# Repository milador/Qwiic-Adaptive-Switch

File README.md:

# Qwiic-Adaptive-Switch

Qwiic-Adaptive-Switch modules provide an easy way to create your own adaptive switch input or output boxes through Qwiic or STEMMA QT ecosystem. Qwiic Adaptive Switch modules can be connected to any Qwiic enabled board to create an adaptive switch box.

You can find more information about <a href="https://www.sparkfun.com/qwiic">Qwiic Connect System</a> at SparkFun official website.

Qwiic-Adaptive-Switch modules use Qwiic/JST-SH-4Pin connector and IC2 interface to communicate with main microcontroller which means you can connect multiple switch modules by daisy chaining them. It's using TCA9534 bus expander.

## Qwiic-Adaptive-Switch-Input

Top View: 

Bottom View:

## Qwiic-Adaptive-Switch-Output

Top View: 

Bottom View:

## Risk Assessment

The Risk Assessment documents are located under [Documents](./Documents/) directory. 

## License

### MIT License

Copyright (c) 2021 milador

Permission is hereby granted, free of charge, to any person obtaining a copy of this software and associated documentation files (the "Software"), to deal in the Software without restriction, including without limitation the rights to use, copy, modify, merge, publish, distribute, sublicense, and/or sell copies of the Software, and to permit persons to whom the Software is furnished to do so, subject to the following conditions:

The above copyright notice and this permission notice shall be included in all copies or substantial portions of the Software.

THE SOFTWARE IS PROVIDED "AS IS", WITHOUT WARRANTY OF ANY KIND, EXPRESS OR IMPLIED, INCLUDING BUT NOT LIMITED TO THE WARRANTIES OF MERCHANTABILITY, FITNESS FOR A PARTICULAR PURPOSE AND NONINFRINGEMENT. IN NO EVENT SHALL THE AUTHORS OR COPYRIGHT HOLDERS BE LIABLE FOR ANY CLAIM, DAMAGES OR OTHER LIABILITY, WHETHER IN AN ACTION OF CONTRACT, TORT OR OTHERWISE, ARISING FROM, OUT OF OR IN CONNECTION WITH THE SOFTWARE OR THE USE OR OTHER DEALINGS IN THE SOFTWARE.

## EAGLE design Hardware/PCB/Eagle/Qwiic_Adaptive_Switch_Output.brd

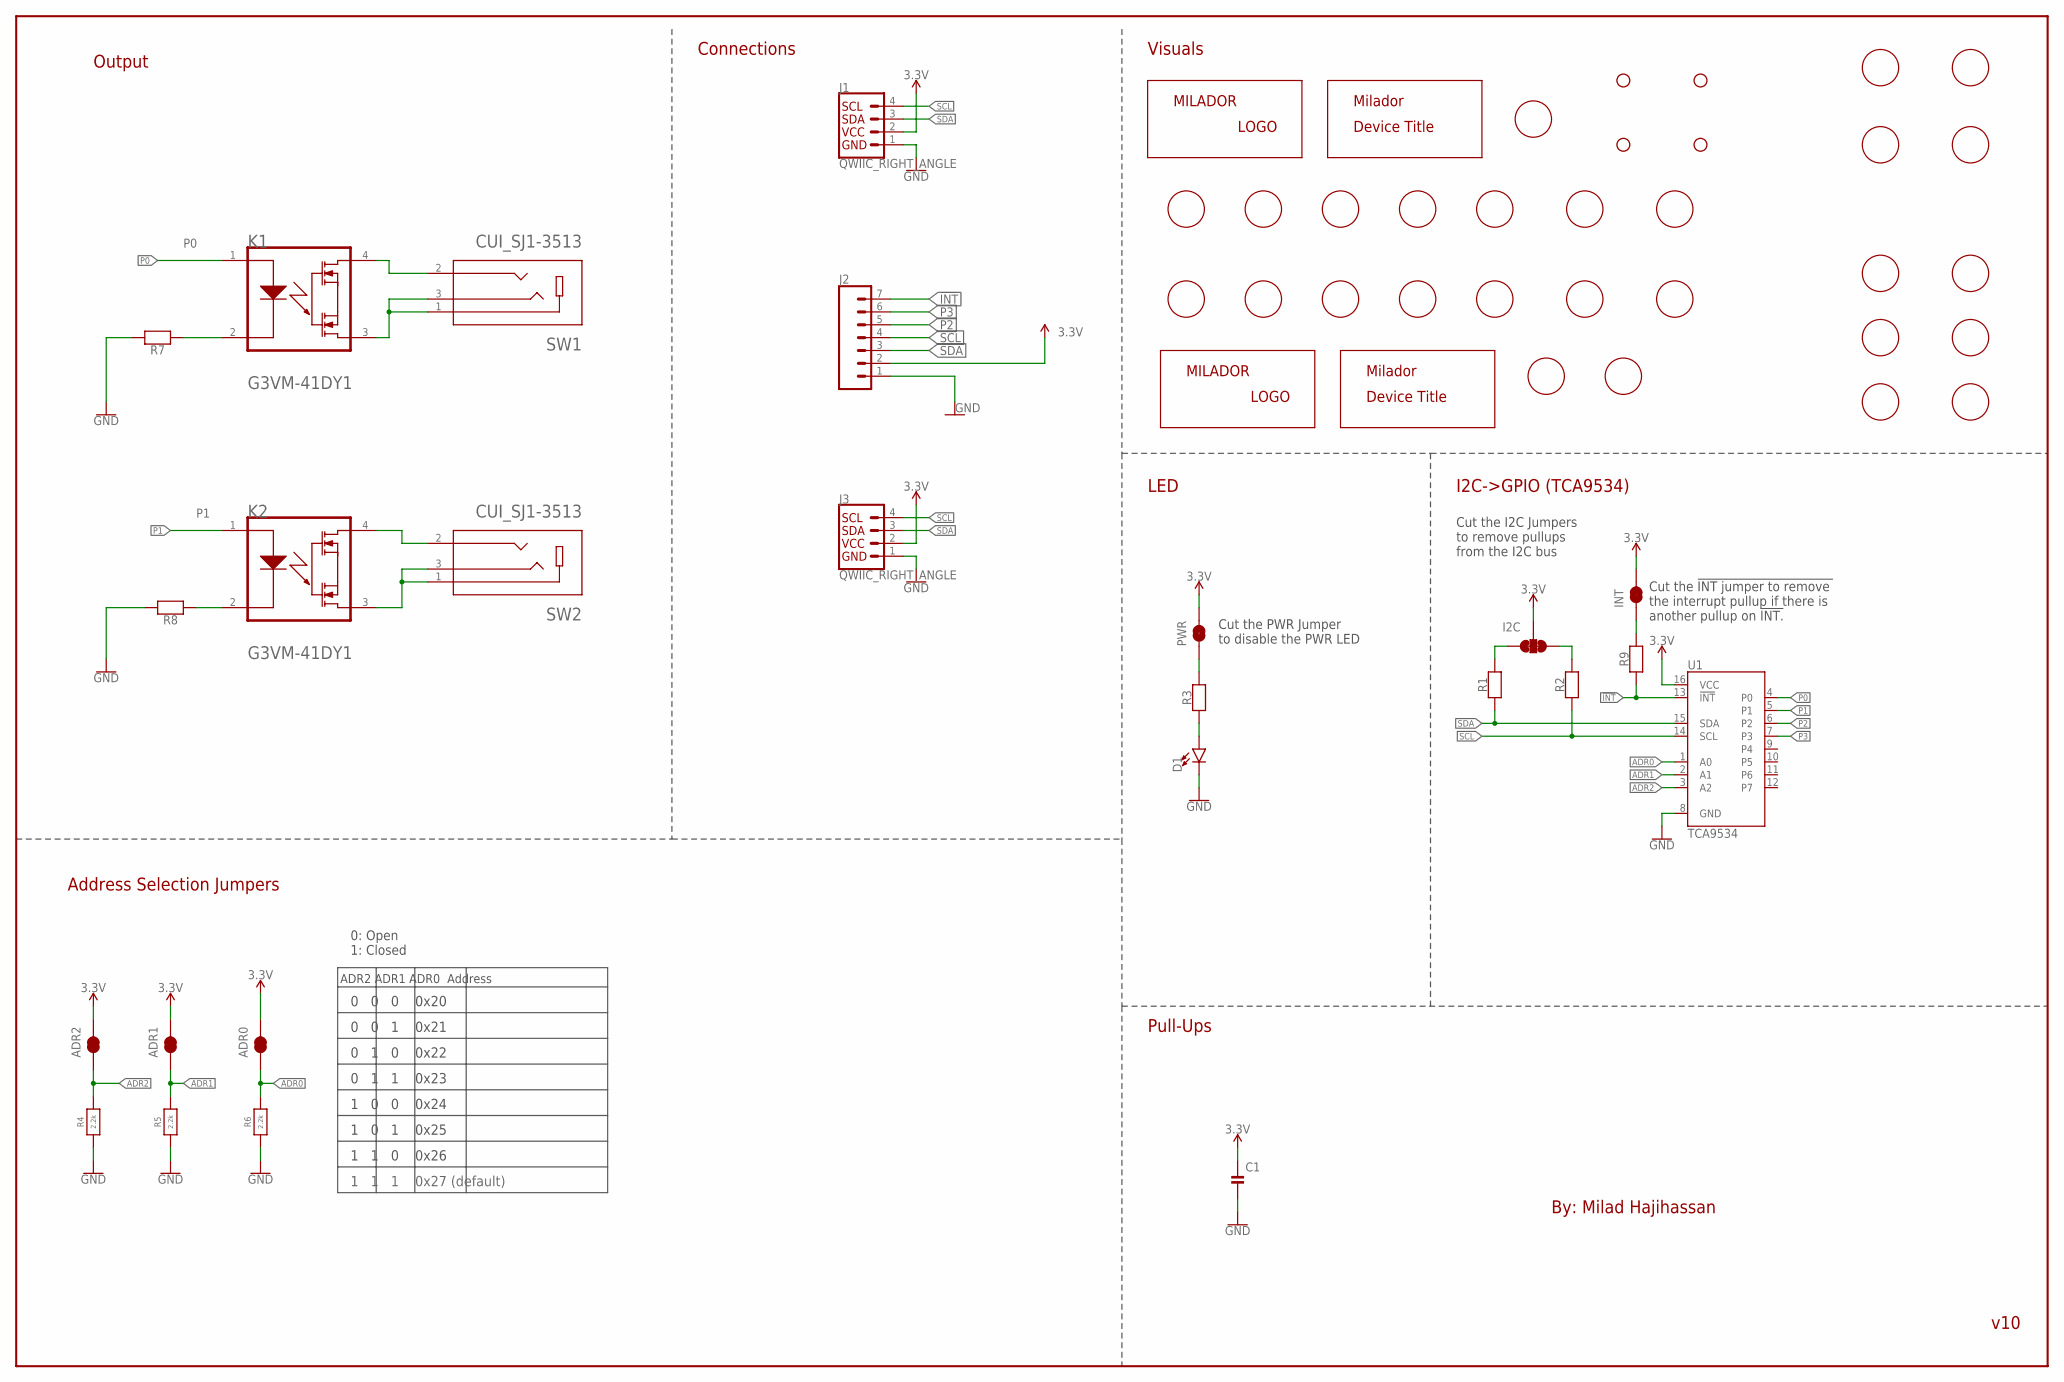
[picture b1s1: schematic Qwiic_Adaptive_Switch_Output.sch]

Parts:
ADR0, ADR1, ADR2: JUMPERS-SMT_2_NC_TRACE_SILK; JUMPERS_SMT-JUMPER_2_NC_TRACE_SILK
C1: 0.1uF; 0805-MP
D1: RED; CHIPLED_0805_NOOUTLINE
H1, H2, H3, H4: STAND-OFF-3.3
I2C: JUMPERS_JUMPER-SMT_3_2-NC_TRACE_SILK; JUMPERS_SMT-JUMPER_3_2-NC_TRACE_SILK
INT: JUMPERS-SMT_2_NC_TRACE_SILK; JUMPERS_SMT-JUMPER_2_NC_TRACE_SILK
J1, J3: QWIIC_RIGHT_ANGLE; CONNECTORS_JST04_1MM_RA
J2: CONNECTORS_CONN_071X07_NO_SILK; CONNECTORS_1X07_NO_SILK
K1, K2: G3VM-41DY1
LABEL_3V_BOTTOM, LABEL_3V_TOP: MILADOR-LABEL-3V; LABEL-3V
LABEL_!INT_BOTTOM: MILADOR-LABEL-!INT; LABEL-!INT
LABEL_!INT_TOP: MILADOR-LABEL-!INT; LABEL-!INT
LABEL_ADR0: MILADOR-LABEL-ADR0; LABEL-ADR0
LABEL_ADR1: MILADOR-LABEL-ADR1; LABEL-ADR1
LABEL_ADR2: MILADOR-LABEL-ADR2; LABEL-ADR2
LABEL_GND_BOTTOM: MILADOR-LABEL-GND; LABEL-GND
LABEL_GND_TOP: MILADOR-LABEL-GND; LABEL-GND
LABEL_I2C: MILADOR-LABEL-I2C; LABEL-I2C
LABEL_I2C_ADDRESS: MILADOR-LABEL-ADDRESS-0X27; LABEL-ADDRESS-27
LABEL_INT: MILADOR-LABEL-INT; LABEL-INT
LABEL_MILADOR_BOTTOM: MILADOR-LOGO-; MILADOR_LOGO1
LABEL_MILADOR_TOP: MILADOR-LOGO-; MILADOR_LOGO1
LABEL_OUTPUT_BOTTOM: MILADOR-SWITCH-NAME-SW-OUTPUT; SWITCH-OUTPUT
LABEL_OUTPUT_TOP: MILADOR-SWITCH-NAME-SW-OUTPUT; SWITCH-OUTPUT
LABEL_P0_BOTTOM: MILADOR-LABEL-P0; LABEL-P0
LABEL_P1_BOTTOM: MILADOR-LABEL-P1; LABEL-P1
LABEL_P2_BOTTOM, LABEL_P2_TOP: MILADOR-LABEL-P2; LABEL-P2
LABEL_P3_BOTTOM, LABEL_P3_TOP: MILADOR-LABEL-P3; LABEL-P3
LABEL_PWR: MILADOR-LABEL-PWR; LABEL-PWR
LABEL_SW1: MILADOR-SWITCH-NAME-SW1; SWITCH-SW1
LABEL_SW2: MILADOR-SWITCH-NAME-SW2; SWITCH-SW2
LABEL_TITLE_BOTTOM: MILADOR-DEVICE-QWIIC-SWITCH; MILADOR_QWIIC_SWITCH
LABEL_TITLE_TOP: MILADOR-DEVICE-QWIIC-SWITCH-SM; MILADOR_QWIIC_SWITCH_SM
LABE_SCL_BOTTOM: MILADOR-LABEL-SCL; LABEL-SCL
LABE_SCL_TOP: MILADOR-LABEL-SCL; LABEL-SCL
LABE_SDA_BOTTOM: MILADOR-LABEL-SDA; LABEL-SDA
LABE_SDA_TOP: MILADOR-LABEL-SDA; LABEL-SDA
PWR: JUMPERS-SMT_2_NC_TRACE_SILK; JUMPERS_SMT-JUMPER_2_NC_TRACE_SILK
R1, R2, R4, R5, R6: 2.2k; 0805-MP
R3: 1k; 0805-MP
R7, R8: 220; 0805-MP
R9: 10k; 0805-MP
SW1, SW2: CUI_SJ1-3513
U1: TCA9534; 16SOIC

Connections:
3.3V: ADR0.2, ADR1.2, ADR2.2, C1.1, I2C.2, INT.2, J1.2, J2.2, J3.2, PWR.2, U1.16 (VCC)
!INT: J2.7, R9.1, U1.13 (!INT)
ADR0: ADR0.1, R6.2, U1.1 (A0)
ADR1: ADR1.1, R5.2, U1.2 (A1)
ADR2: ADR2.1, R4.2, U1.3 (A2)
GND: C1.2, D1.C, J1.1, J2.1, J3.1, R4.1, R5.1, R6.1, R7.2, R8.2, U1.8 (GND)
unnamed: INT.1, R9.2
unnamed: D1.A, R3.1
unnamed: PWR.1, R3.2
unnamed: K1.4, SW1.2
unnamed: K1.2, R7.1
unnamed: K1.3, SW1.1, SW1.3
unnamed: K2.2, R8.1
unnamed: K2.4, SW2.2
unnamed: K2.3, SW2.1, SW2.3
P0: K1.1, U1.4 (P0)
P1: K2.1, U1.5 (P1)
P2: J2.5, U1.6 (P2)
P3: J2.6, U1.7 (P3)
SCL: J1.4, J2.4, J3.4, R2.1, U1.14 (SCL)
SCL_PU1: I2C.1, R1.2
SDA: J1.3, J2.3, J3.3, R1.1, U1.15 (SDA)
SDA_PU1: I2C.3, R2.2

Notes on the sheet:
v10
Address Selection Jumpers
ADR2 ADR1 ADR0 Address
0 0 0 0x20
0 0 1 0x21
0 1 0 0x22
0 1 1 0x23
1 0 0 0x24
1 0 1 0x25
1 1 0 0x26
1 1 1 0x27 (default)
0: Open 1: Closed
I2C->GPIO (TCA9534)
Connections
By: Milad Hajihassan
Cut the !INT jumper to remove the interrupt pullup if there is another pullup on !INT.
Cut the I2C Jumpers to remove pullups from the I2C bus
Cut the PWR Jumper to disable the PWR LED
LED
Visuals
Pull-Ups
Output

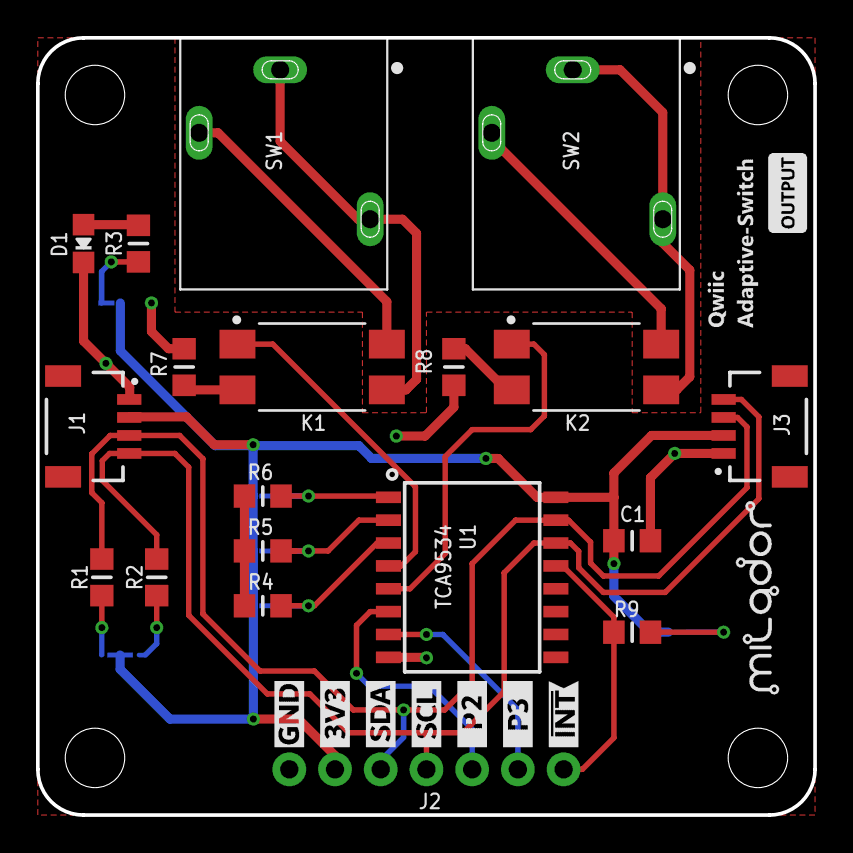
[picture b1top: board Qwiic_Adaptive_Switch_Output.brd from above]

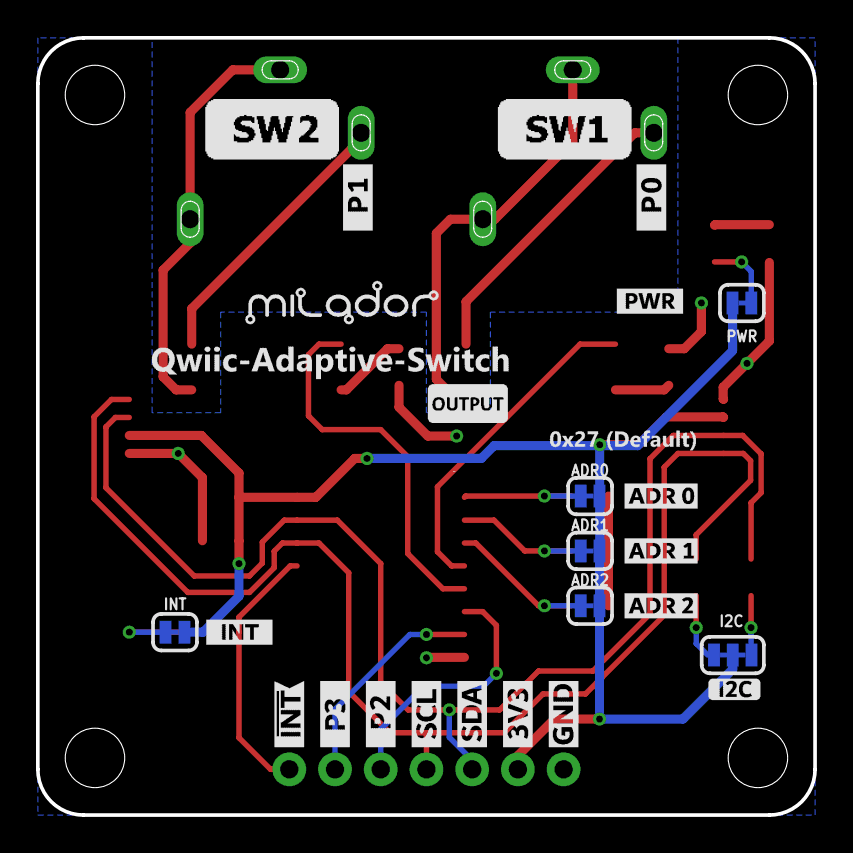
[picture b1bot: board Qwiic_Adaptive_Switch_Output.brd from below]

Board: 2 copper layers, 43.2 x 43.2 mm, 60 parts (27 on the bottom side), 23 nets.

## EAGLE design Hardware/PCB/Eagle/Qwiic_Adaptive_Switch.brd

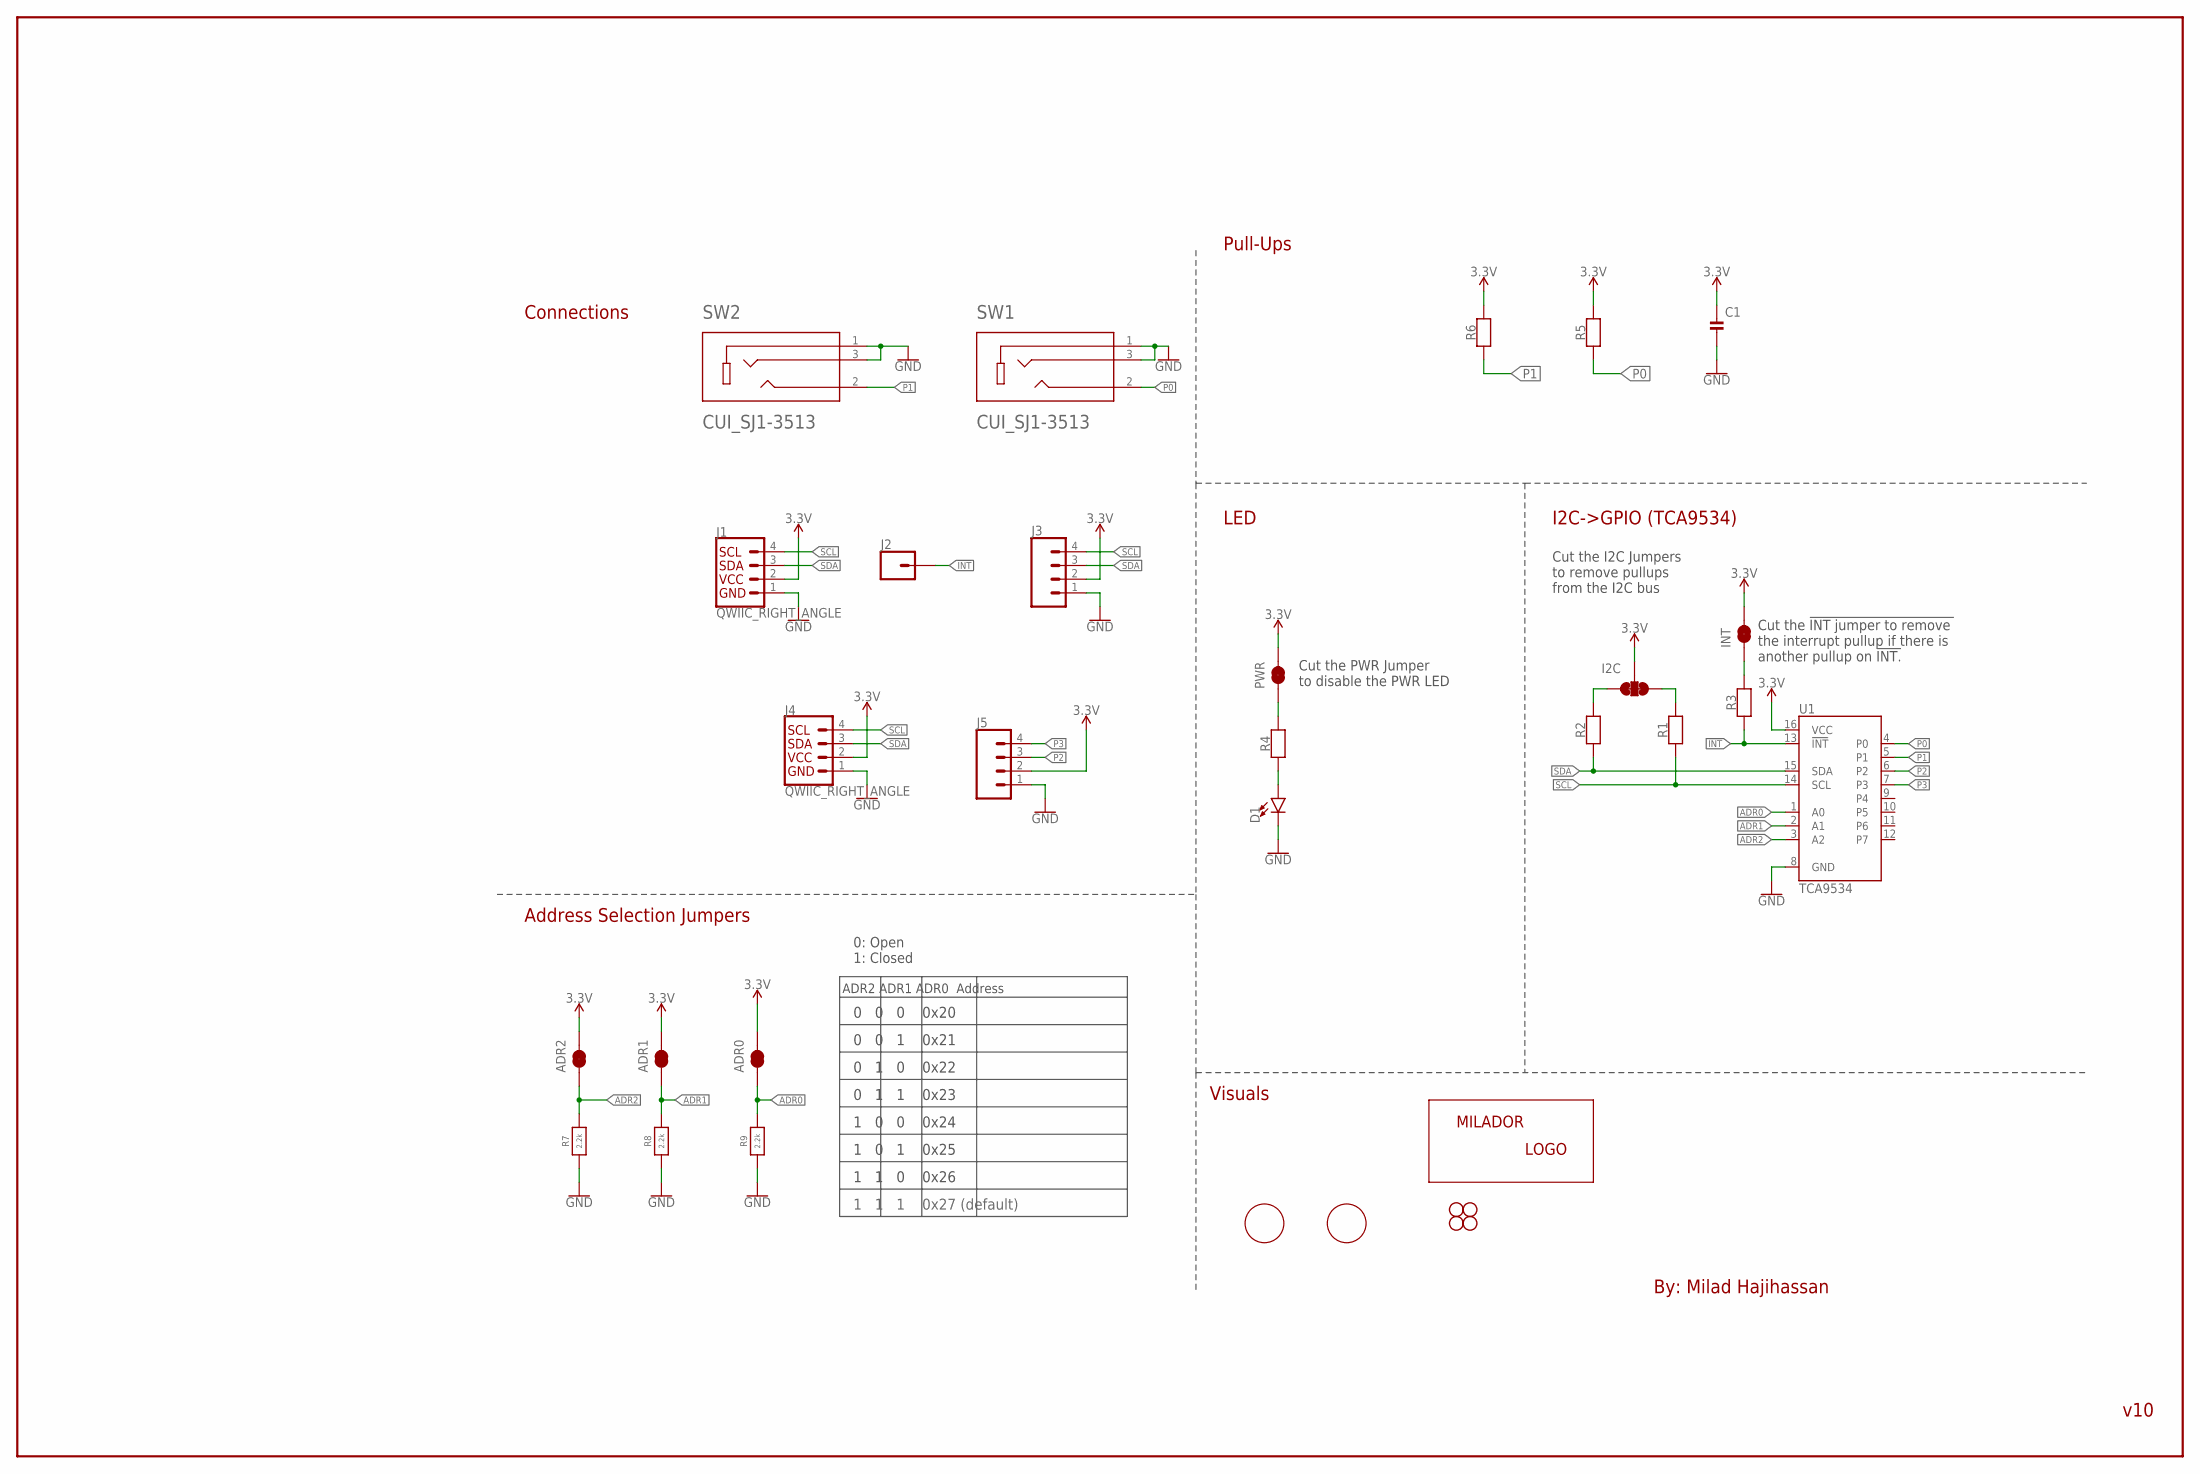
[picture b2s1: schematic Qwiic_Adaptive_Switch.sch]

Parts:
ADR0, ADR1, ADR2: JUMPERS-SMT_2_NC_TRACE_SILK; JUMPERS_SMT-JUMPER_2_NC_TRACE_SILK
C1: 0.1uF; 0603
D1: RED; LED-0603
H1, H2: STAND-OFF
I2C: JUMPERS_JUMPER-SMT_3_2-NC_TRACE_SILK; JUMPERS_SMT-JUMPER_3_2-NC_TRACE_SILK
INT: JUMPERS-SMT_2_NC_TRACE_SILK; JUMPERS_SMT-JUMPER_2_NC_TRACE_SILK
J1, J4: QWIIC_RIGHT_ANGLE; CONNECTORS_JST04_1MM_RA
J2: CONNECTORS_CONN_01PTH_NO_SILK_YES_STOP; CONNECTORS_1X01_NO_SILK
J3, J5: CONNECTORS_CONN_041X04_NO_SILK; CONNECTORS_1X04_NO_SILK
JP3, JP4: STAND-OFF
PWR: JUMPERS-SMT_2_NC_TRACE_SILK; JUMPERS_SMT-JUMPER_2_NC_TRACE_SILK
R1, R2, R7, R8, R9: 2.2k; 0603
R3, R5: 10k; 0603
R4: 1k; 0603
R6: 10K; 0603
SW1, SW2: CUI_SJ1-3513
U1: TCA9534; 16SOIC
U$6: MILADOR-LOGO-; MILADOR_LOGO1
U$17: MILADOR-SWITCH-NAME-SW1; SWITCH-SW1
U$18: MILADOR-SWITCH-NAME-SW2; SWITCH-SW2

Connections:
3.3V: ADR0.2, ADR1.2, ADR2.2, C1.1, I2C.2, INT.2, J1.2, J3.2, J4.2, J5.2, PWR.2, R5.2, R6.2, U1.16 (VCC)
!INT: J2.1, R3.1, U1.13 (!INT)
ADR0: ADR0.1, R9.2, U1.1 (A0)
ADR1: ADR1.1, R8.2, U1.2 (A1)
ADR2: ADR2.1, R7.2, U1.3 (A2)
GND: C1.2, D1.C, J1.1, J3.1, J4.1, J5.1, R7.1, R8.1, R9.1, SW1.1, SW1.3, SW2.1, SW2.3, U1.8 (GND)
unnamed: INT.1, R3.2
unnamed: D1.A, R4.1
unnamed: PWR.1, R4.2
P0: R5.1, SW1.2, U1.4 (P0)
P1: R6.1, SW2.2, U1.5 (P1)
P2: J5.3, U1.6 (P2)
P3: J5.4, U1.7 (P3)
SCL: J1.4, J3.4, J4.4, R1.1, U1.14 (SCL)
SCL_PU1: I2C.1, R2.2
SDA: J1.3, J3.3, J4.3, R2.1, U1.15 (SDA)
SDA_PU1: I2C.3, R1.2

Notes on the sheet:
v10
Address Selection Jumpers
ADR2 ADR1 ADR0 Address
0 0 0 0x20
0 0 1 0x21
0 1 0 0x22
0 1 1 0x23
1 0 0 0x24
1 0 1 0x25
1 1 0 0x26
1 1 1 0x27 (default)
0: Open 1: Closed
I2C->GPIO (TCA9534)
Connections
By: Milad Hajihassan
Cut the !INT jumper to remove the interrupt pullup if there is another pullup on !INT.
Cut the I2C Jumpers to remove pullups from the I2C bus
Cut the PWR Jumper to disable the PWR LED
LED
Visuals
Pull-Ups

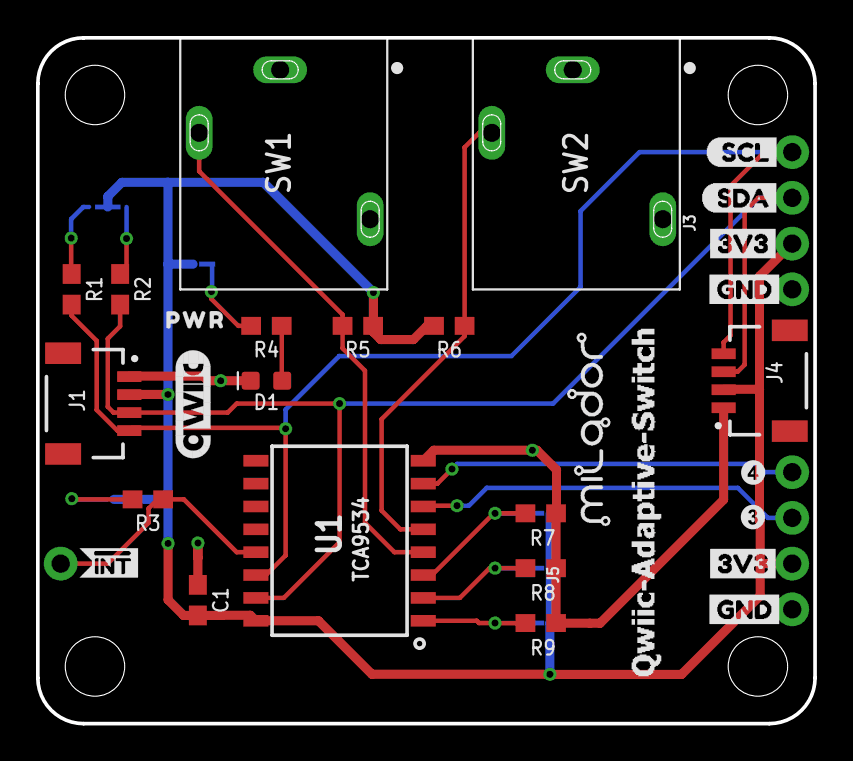
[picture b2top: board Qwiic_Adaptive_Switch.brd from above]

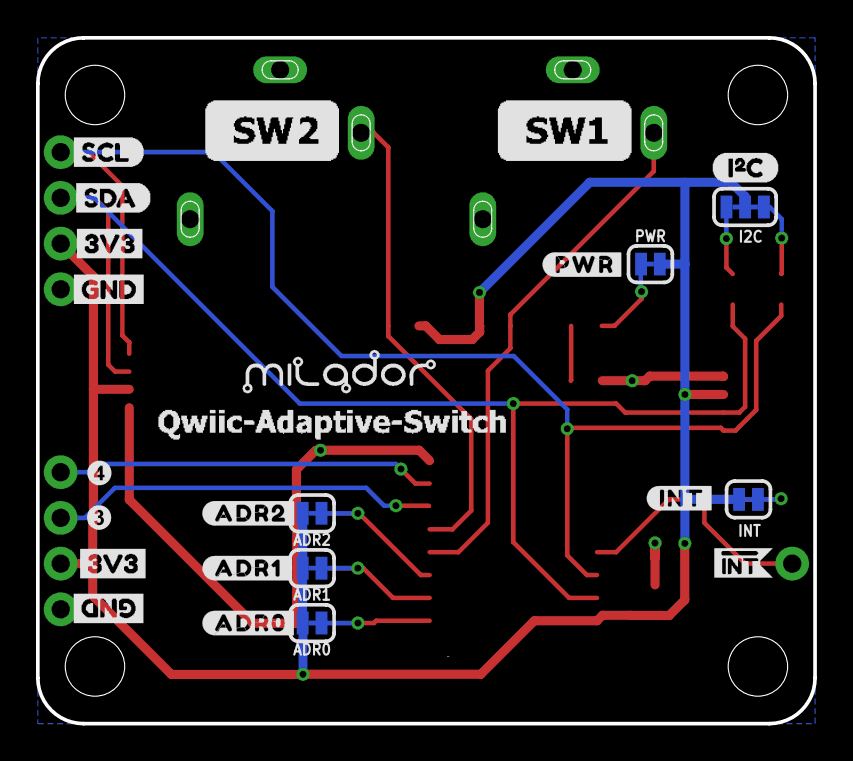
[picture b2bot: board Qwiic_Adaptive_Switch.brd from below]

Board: 2 copper layers, 43.2 x 38.1 mm, 57 parts (23 on the bottom side), 17 nets.

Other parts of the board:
U$1: I2C
U$2, U$7, U$14, U$25: GND4
U$3, U$4, U$8, U$26: 3V33
U$5: #ADR1#0
U$9: SCL6
U$10: SDA5
U$11: #ADR2#0
U$12: #INT#0
U$13, U$22: #INT0
U$15: #ADR0#0
U$16, U$19: MILADOR_QWIIC_SWITCH
U$20: MILADOR-LOGO-; MILADOR_LOGO1
U$21: QWIIC_6MM
U$23: SCL0
U$24: SDA1
U$34: PWR0
U$39: #PWR#0

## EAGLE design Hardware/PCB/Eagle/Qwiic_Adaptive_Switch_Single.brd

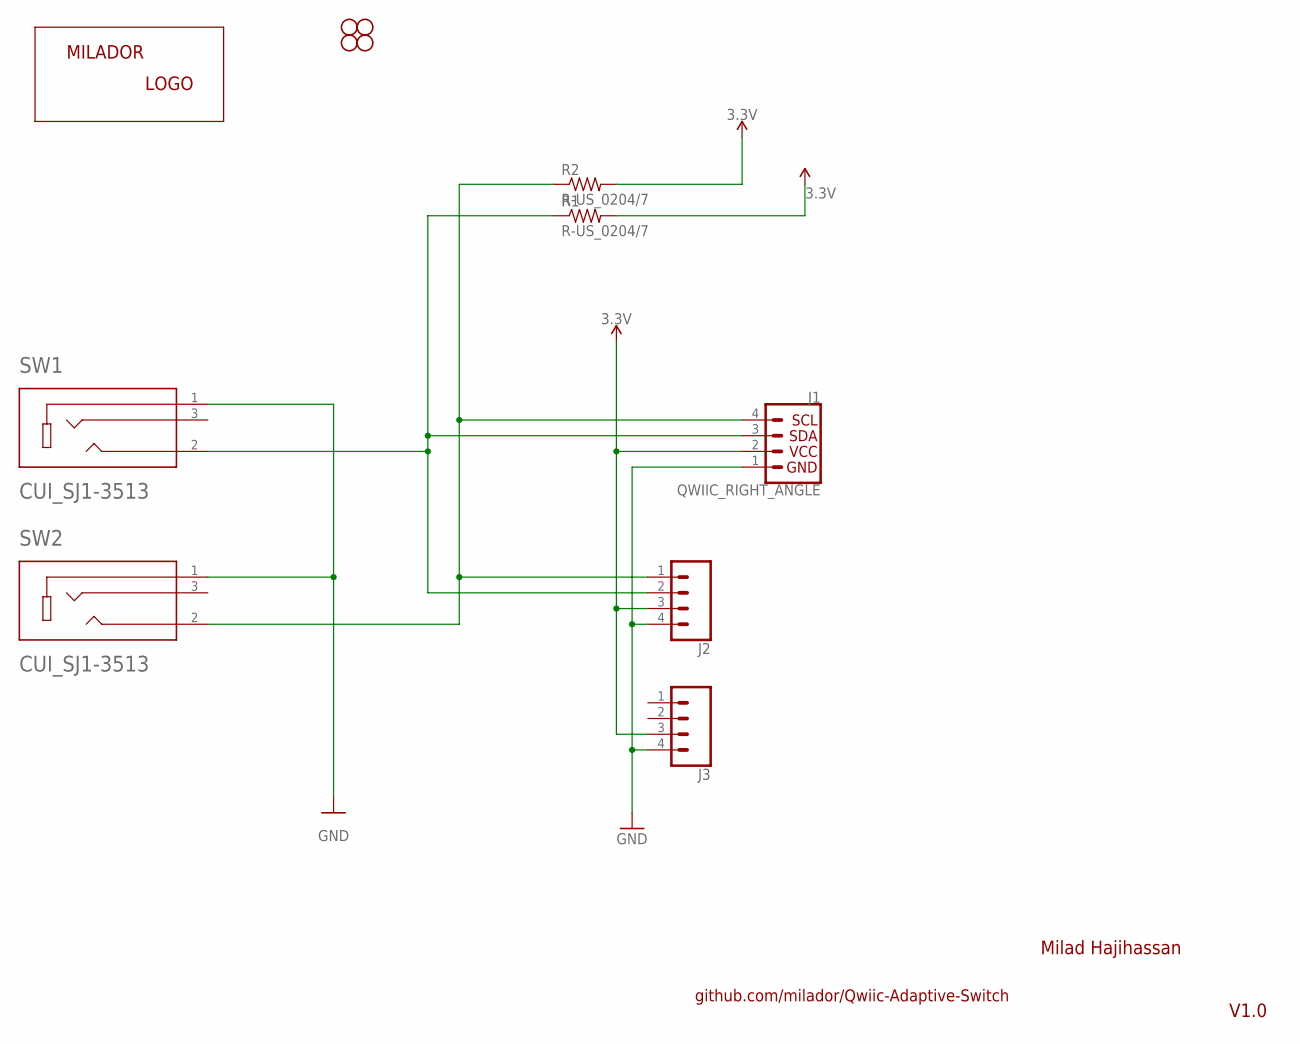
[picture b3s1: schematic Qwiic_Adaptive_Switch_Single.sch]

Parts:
J1: QWIIC_RIGHT_ANGLE; CONNECTORS_JST04_1MM_RA
J2: J2; CONNECTORS_1X04_NO_SILK
J3: CONNECTORS_CONN_041X04_NO_SILK; CONNECTORS_1X04_NO_SILK
JP1, JP2, JP3, JP4: STAND-OFF
R1, R2: R-US_0204/7; 0204/7
SW1, SW2: CUI_SJ1-3513
U$2: MILADOR-LOGO-; MILADOR_LOGO1

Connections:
3.3V: J1.2, J2.3, J3.3, R1.2, R2.2
GND: J1.1, J2.4, J3.4, SW1.1, SW2.1
SCL/SCK: J1.4, J2.1, R2.1, SW2.2
SDA/MOSI: J1.3, J2.2, R1.1, SW1.2

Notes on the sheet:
V1.0
Milad Hajihassan
github.com/milador/Qwiic-Adaptive-Switch

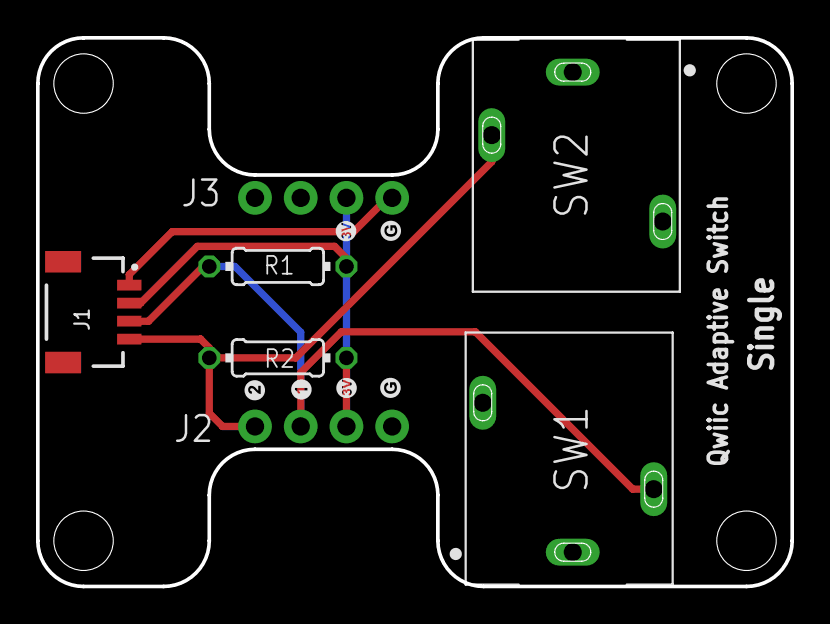
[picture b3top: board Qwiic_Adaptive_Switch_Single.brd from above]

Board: 2 copper layers, 41.9 x 30.5 mm, 12 parts (1 on the bottom side), 4 nets.

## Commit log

2021-01-07 Added BOM file
2021-01-07 Added Eagle PCB Design files
2021-01-07 Added Gerber files
2021-01-07 Added Art Works
2021-01-07 Added 3D Model images
2021-01-07 Added description
2021-01-07 Updated BOM File
2021-01-07 Added link to Qwiic Connect System website
2021-01-08 Updated part list
2021-01-09 Added Single and I2C BOM files
2021-01-09 Updated readme to explain two versions
2021-01-09 Update silkscreen
2021-01-09 Added pictures of PCB 3D model
2021-04-21 Updated BOM
2021-05-30 Updated design
2021-06-05 Updated the design.
2021-07-08 Updated the design - Stable design
2021-07-11 Added Arduino example
2021-09-05 Renamed the module
2021-09-05 Updated documentation
2021-09-05 Updated PCB
2021-09-07 Added Switch Output
2021-09-07 Updated PCB Designs to match input with output designs
2021-09-11 Updated PCB Mount holes
2021-09-14 Updated footprints to 0805 packages
2021-09-18 Updated silkscreen
2021-10-31 Added sample output code
2021-10-31 Added more information about the software options
2021-12-13 Updated design to version 1.2
2021-12-13 Updated version 2.1 BOM
2021-12-13 Removed Images
2021-12-13 Added version 1.2 images
2021-12-19 Updated header pin order
2022-02-10 Updated code for different output module address
2022-04-04 Added step files
2023-04-10 Added Risk Assessment documents

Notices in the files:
parts and their libraries:
SparkFun-Aesthetics: Licensing: Creative Commons ShareAlike 4.0 International - https://creativecommons.org/licenses/by-sa/4.0
